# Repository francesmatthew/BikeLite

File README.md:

## BikeLite

This is the schematic and PCB for a buck converter and 555 timer to add flashing LEDs to my bike.

The output voltage is 5.2V, (theoretically) capable of up to 2A

(5.2V is the combined forward voltage of a white and red LED in series)

The PCB contains connections for two switches: 1) enable and 2) flash disable

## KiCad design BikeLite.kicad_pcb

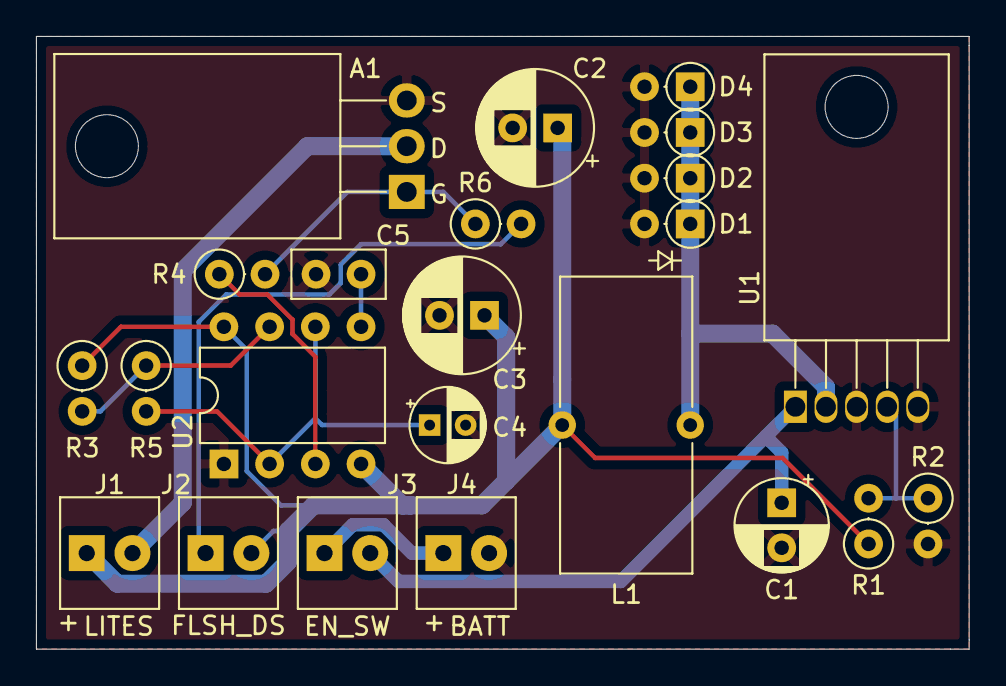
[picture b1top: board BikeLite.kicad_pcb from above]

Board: 2 copper layers, 51.8 x 34.0 mm, 23 parts (0 on the bottom side), 13 nets.

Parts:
A1: FQP30N06; TO-220-3_Horizontal_TabDown
C1: 100uF; CP_Radial_D5.0mm_P2.50mm
C2, C3: 470uF; CP_Radial_D6.3mm_P2.50mm
C4: 4.7uF; CP_Radial_D4.0mm_P2.00mm
C5: 10nF; C_Disc_D5.0mm_W2.5mm_P2.50mm
D1, D2, D3, D4: D; D_DO-35_SOD27_P2.54mm_Vertical_AnodeUp
J1, J2, J3, J4: Screw_Terminal_01x02; Screw_Terminal
L1: 100uH; L_Toroid_Vertical_L16.3mm_W7.1mm_P7.11mm_Pulse_H
R1: 2.2k; R_Axial_DIN0207_L6.3mm_D2.5mm_P2.54mm_Vertical
R2: 680; R_Axial_DIN0207_L6.3mm_D2.5mm_P2.54mm_Vertical
R3, R4, R6: 10k; R_Axial_DIN0207_L6.3mm_D2.5mm_P2.54mm_Vertical
R5: 100k; R_Axial_DIN0207_L6.3mm_D2.5mm_P2.54mm_Vertical
U1: LM2576HVT-ADJ; TO-220-5_Horizontal_TabDown
U2: NE555P; DIP-8_W7.62mm

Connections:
BATT_IN: J3.1, J4.1
FB: R1.2, R2.1, U1.4
GND: A1.3, C1.2, C2.2, C3.2, C4.2, C5.2, D1.2, D2.2, D3.2, D4.2, J4.2, R2.2, U1.3, U1.5, U2.1
LITE-: A1.2, J1.2
LITE_EN: A1.1, R4.2, R6.1
unnamed: C4.1, R5.2, U2.2, U2.6
unnamed: C5.1, U2.5
unnamed: D1.1, D2.1, D3.1, D4.1, L1.2, U1.2
unnamed: J2.1, R6.2
unnamed: R3.2, R5.1, U2.7
unnamed: R4.1, U2.3
V_in: C1.1, J3.2, U1.1
V_out: C2.1, C3.1, J1.1, J2.2, L1.1, R1.1, R3.1, U2.4, U2.8

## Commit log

2021-12-29 Inital Commit
2022-01-20 Revision B
    -Updated screw terminal dimensions and silkscreen labels
    -Changed flash_disable signal to directly enable the MOSFET
    -Updated inductor footprint dimensions
    -Added schematic information on the silkscreen
